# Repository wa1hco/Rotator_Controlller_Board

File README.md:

# Rotator_Controlller_Board
Board, Teensy, Relays for Ham M type rotators

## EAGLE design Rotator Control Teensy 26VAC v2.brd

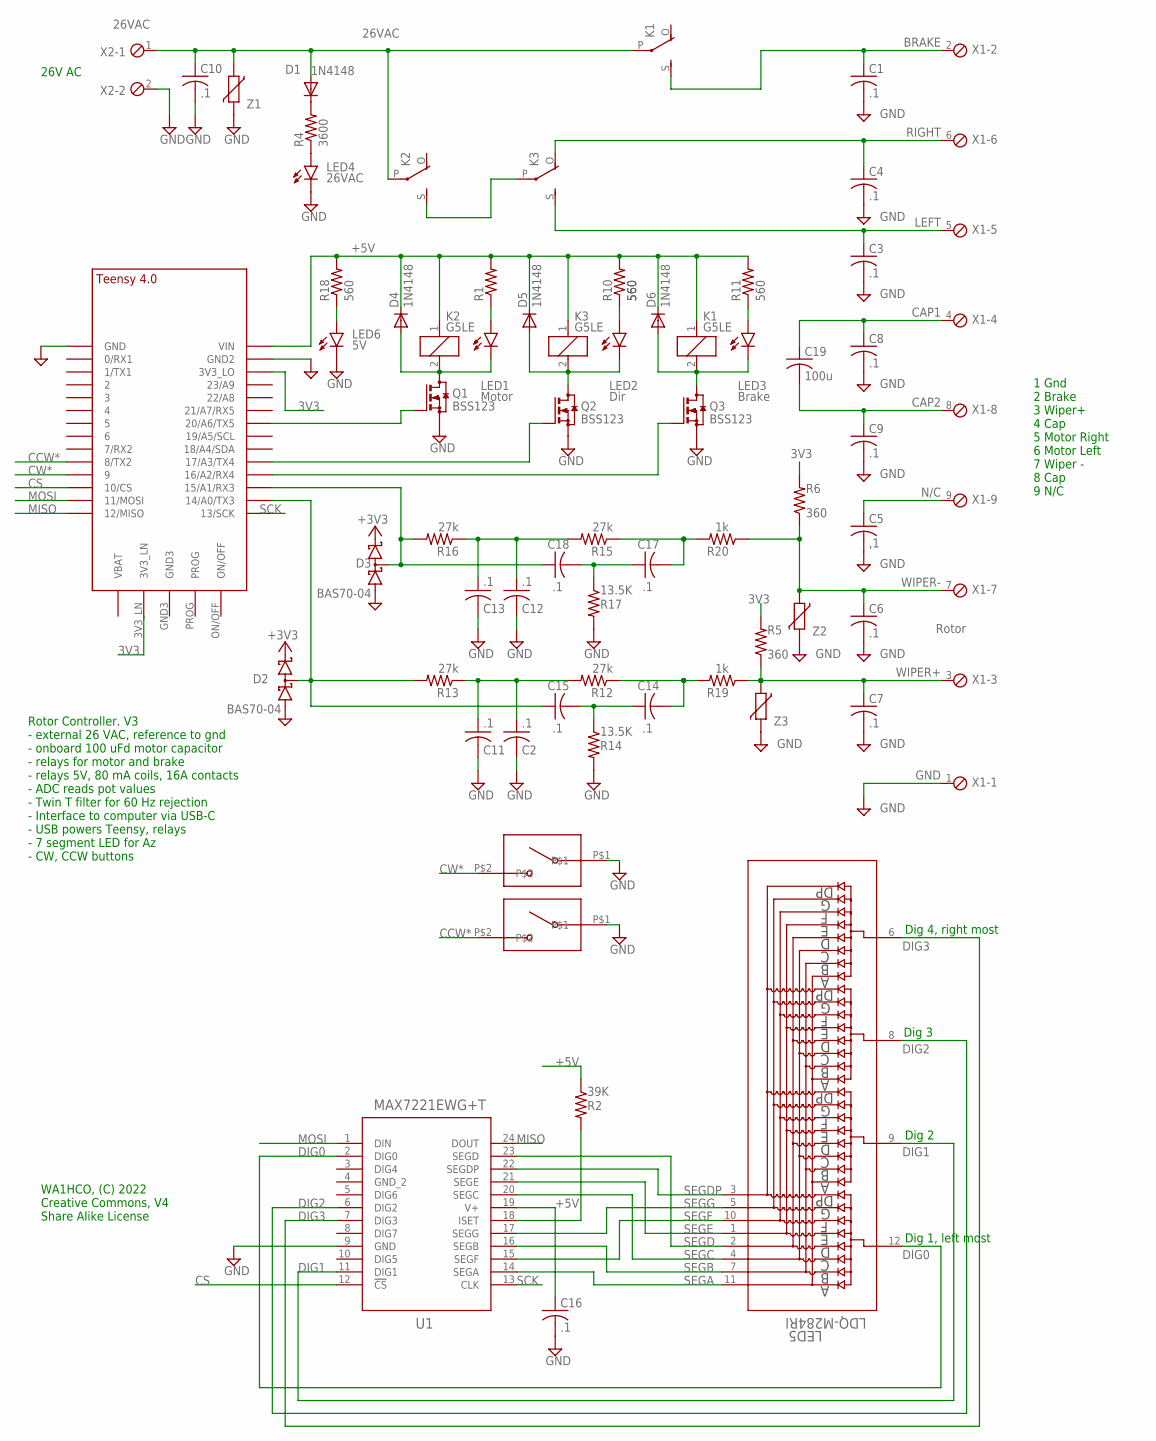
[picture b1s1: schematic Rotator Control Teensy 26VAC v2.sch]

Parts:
C1, C2, C3, C4, C6, C7, C8, C9, C10, C11, C12, C13, C14, C15, C16, C17, C18: .1; C1206
C5: ,1; C1206
C19: 100u; C4220
CCW: SWITCH_AEXIT_6X6X9.5; PUSHBUTTON_6X6
CW: SWITCH_AEXIT_6X6X9.5; PUSHBUTTON_6X6
D1, D4, D5, D6: 1N4148; SOD-123
D2, D3: BAS70-04; SOT23
K1, K2, K3: G5LE
LED1: Motor; LED3MM
LED2: Dir; LED3MM
LED3: Brake; LED3MM
LED4: 26VAC; LED3MM
LED5: LDQ-M284RI; LDQ-M284RI_LUM
LED6: 5V; LED3MM
Q1, Q2, Q3: BSS123; SOT23
R1, R10, R11, R18: 560; R0805
R2: 39K; R0603
R4: 3600; R0805
R5, R6: 360; R0805
R12, R13, R15, R16: 27k; R0805
R14, R17: 13.5K; R0805
R19, R20: 1k; R0805
U1: MAX7221EWG+T; 21-0042_W24+1_MXM
U$1: TEENSY_4.0
X1: Rotor; 9POL254
X2: 26VAC; 2POL254
Z1, Z2, Z3: VARISTORCN1206; CT/CN1206

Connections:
3V3: D2.2 (C2), D3.2 (C2), R5.2, R6.2, U$1.3V3_LN, U$1.3V3_LO
26VAC: C10.1, D1.A, K1.P, K2.P, X2.1, Z1.1
+5V: C16.1, D4.C, D5.C, D6.C, K1.1, K2.1, K3.1, R1.2, R2.1, R10.2, R11.2, R18.2, U1.19 (V+), U$1.VIN
BRAKE: C1.1, K1.S, X1.2
CAP1: C8.1, C19.P$1 (1), X1.4
CAP2: C9.1, C19.P$2 (2), X1.8
CCW*: CCW.P$2, U$1.8 (8/TX2)
CS: U1.12 (!CS), U$1.10/CS
CW*: CW.P$2, U$1.9/CS (9)
DIG0: LED5.12, U1.2 (DIG0)
DIG1: LED5.9, U1.11 (DIG1)
DIG2: LED5.8, U1.6 (DIG2)
DIG3: LED5.6, U1.7 (DIG3)
GND: C1.2, C2.2, C3.2, C4.2, C5.2, C6.2, C7.2, C8.2, C9.2, C10.2, C11.2, C12.2, C13.2, C16.2, CCW.P$1, CW.P$1, D2.1 (A1), D3.1 (A1), LED4.K (C), LED6.K (C), Q1.2 (S), Q2.2 (S), Q3.2 (S), R14.2, R17.2, U1.9 (GND), U$1.GND, U$1.GND2, X1.1, X2.2, Z1.2, Z2.2, Z3.2
ISET: R2.2, U1.18 (ISET)
LEFT: C4.1, K3.O, X1.6
MISO: U1.24 (DOUT), U$1.12/MISO
MOSI: U1.1 (DIN), U$1.11/MOSI
unnamed: C17.2, R15.1, R20.2
unnamed: LED6.A, R18.1
unnamed: C14.2, R12.1, R19.2
unnamed: LED1.A, R1.1
unnamed: LED2.A, R10.1
unnamed: LED3.A, R11.1
unnamed: C15.1, D2.3 (C1A2), R13.2, U$1.14/A0 (14/A0/TX3)
unnamed: K2.S, K3.P
unnamed: D4.A, K2.2, LED1.K (C), Q1.3 (D)
unnamed: D5.A, K3.2, LED2.K (C), Q2.3 (D)
unnamed: D6.A, K1.2, LED3.K (C), Q3.3 (D)
unnamed: Q3.1 (G), U$1.16/A2 (16/A2/RX4)
unnamed: Q1.1 (G), U$1.20/A6 (20/A6/TX5)
unnamed: Q2.1 (G), U$1.17/A3 (17/A3/TX4)
unnamed: C2.1, C11.1, R12.2, R13.1
unnamed: C14.1, C15.2, R14.1
unnamed: C12.1, C13.1, R15.2, R16.1
unnamed: C17.1, C18.2, R17.1
unnamed: C18.1, D3.3 (C1A2), R16.2, U$1.15/A1 (15/A1/RX3)
unnamed: D1.C, R4.2
unnamed: LED4.A, R4.1
N/C: C5.1, X1.9
RIGHT: C3.1, K3.S, X1.5
SCK: U1.13 (CLK), U$1.13/SCK
SEGA: LED5.11, U1.14 (SEGA)
SEGB: LED5.7, U1.16 (SEGB)
SEGC: LED5.4, U1.20 (SEGC)
SEGD: LED5.2, U1.23 (SEGD)
SEGDP: LED5.3, U1.22 (SEGDP)
SEGE: LED5.1, U1.21 (SEGE)
SEGF: LED5.10, U1.15 (SEGF)
SEGG: LED5.5, U1.17 (SEGG)
WIPER+: C7.1, R5.1, R19.1, X1.3, Z3.1
WIPER-: C6.1, R6.1, R20.1, X1.7, Z2.1

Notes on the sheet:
Rotor Controller. V3 - external 26 VAC, reference to gnd - onboard 100 uFd motor capacitor - relays for motor and brake - relays 5V, 80 mA coils, 16A contacts - ADC reads pot values - Twin T filter for 60 Hz rejection - Interface to computer via USB-C - USB powers Teensy, relays - 7 segment LED for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
1 Gnd 2 Brake 3 Wiper+ 4 Cap 5 Motor Right 6 Motor Left 7 Wiper - 8 Cap 9 N/C
26V AC
WA1HCO, (C) 2022 Creative Commons, V4 Share Alike License
Dig 4, right most
Dig 3
Dig 2
Dig 1, left most

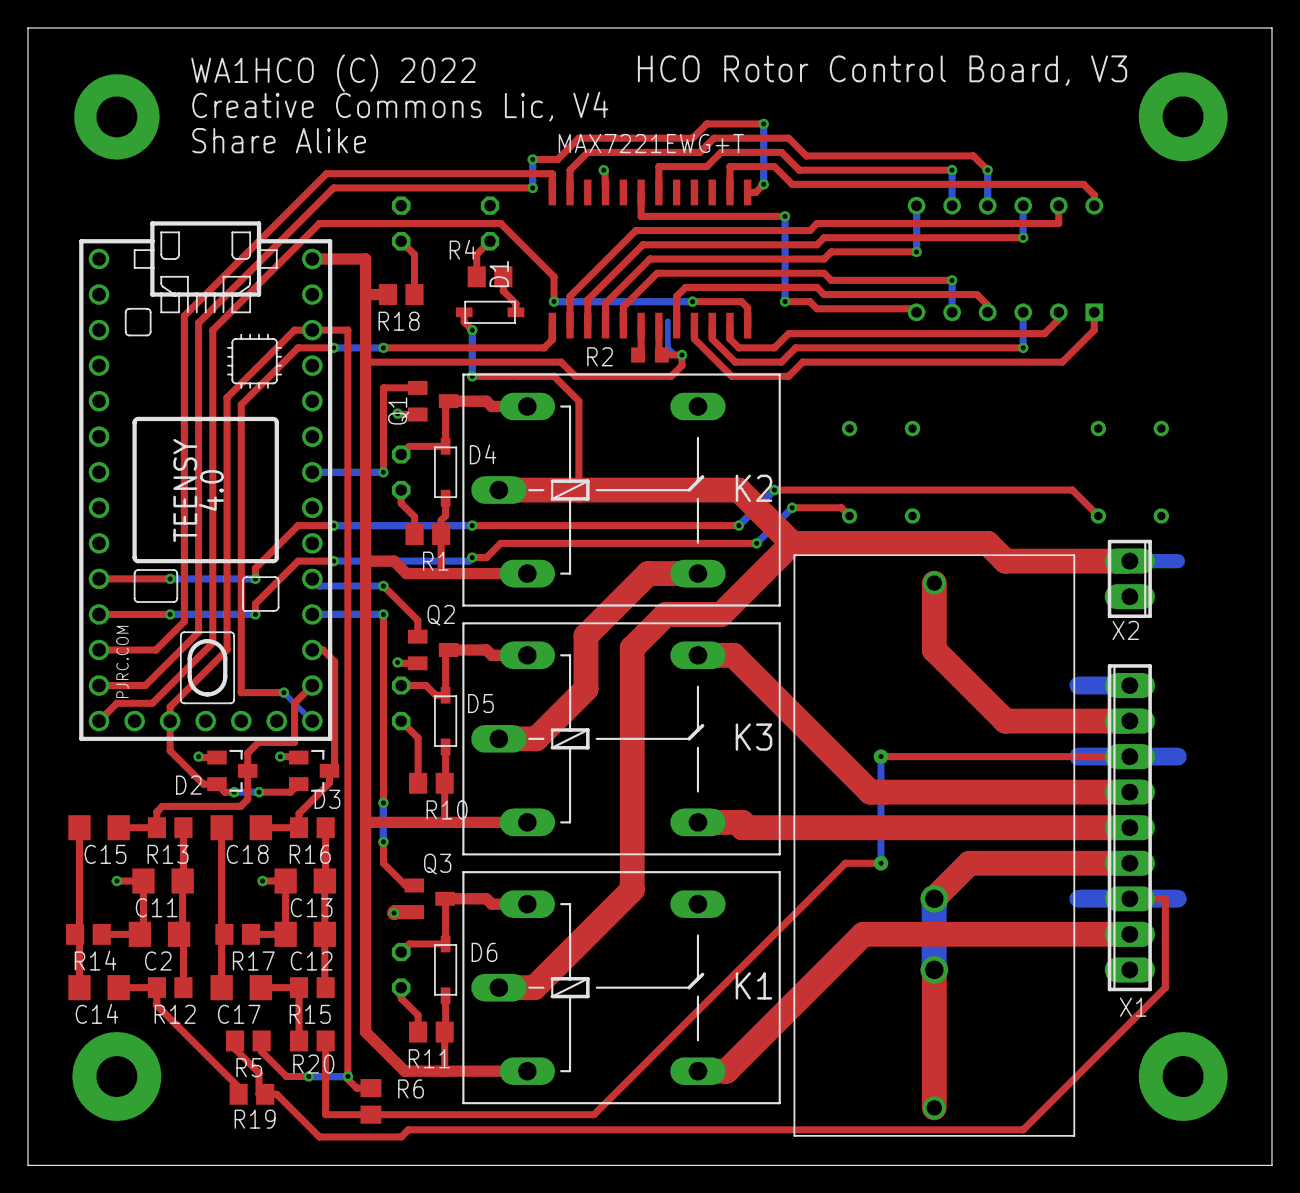
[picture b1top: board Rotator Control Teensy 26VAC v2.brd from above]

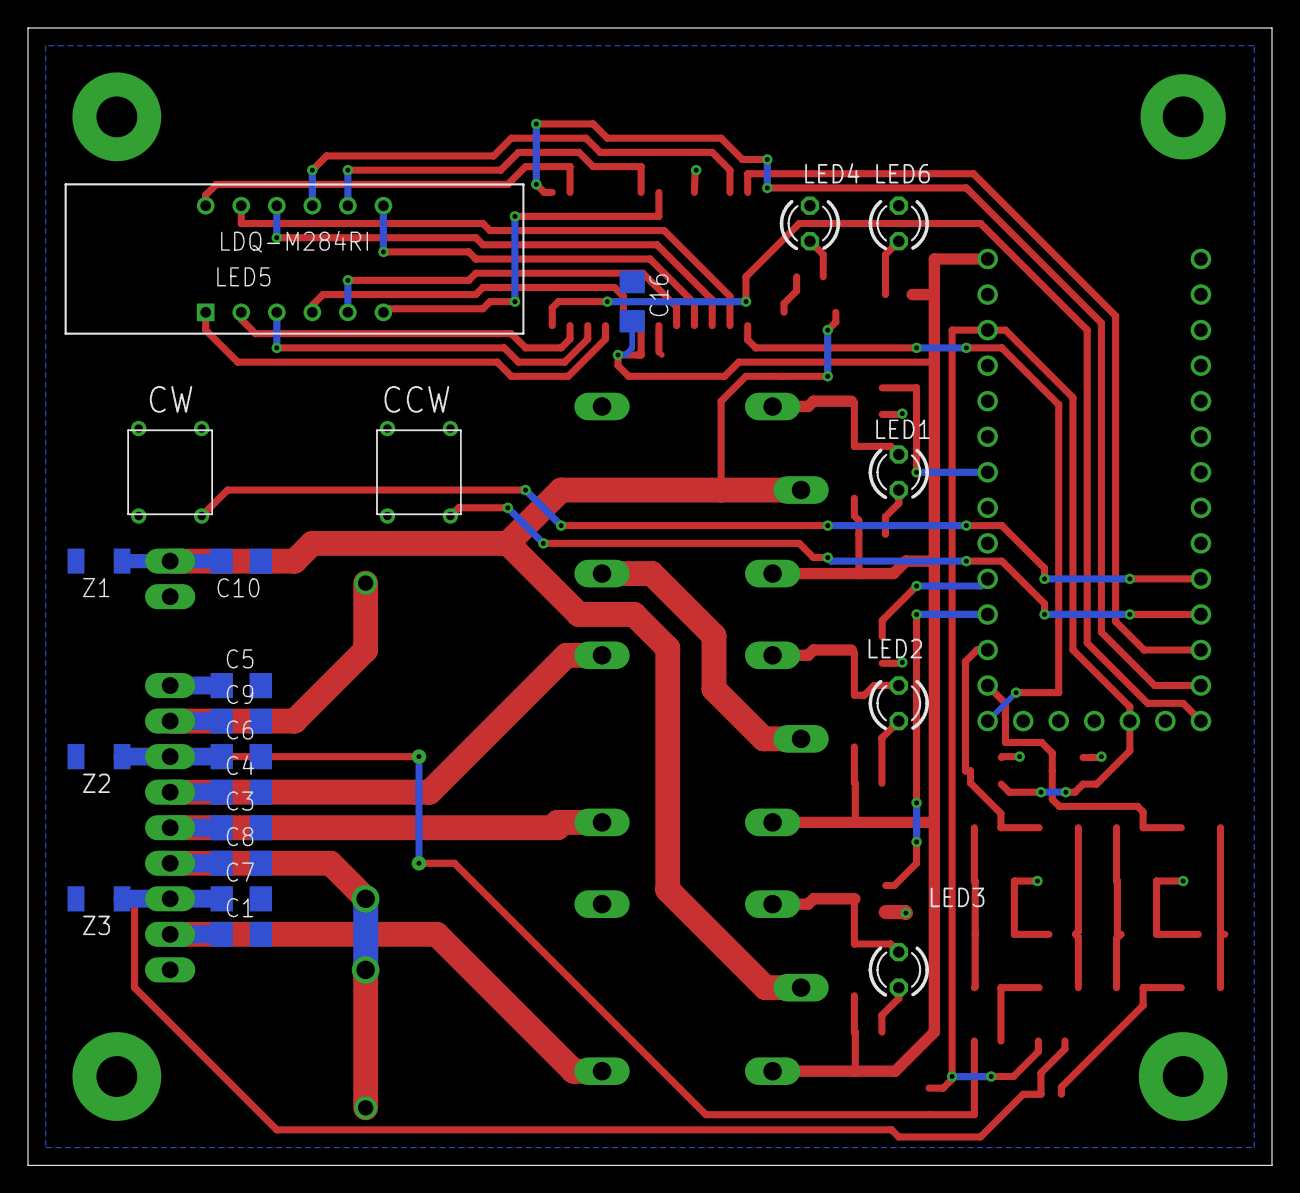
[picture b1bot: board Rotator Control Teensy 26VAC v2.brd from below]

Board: 2 copper layers, 88.9 x 81.3 mm, 62 parts (21 on the bottom side), 52 nets.

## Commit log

2022-03-11 Initial commit of Rotator Controller Board Teensy 4.0 processor, powered from USB C External 36 V AC transformer Relays for rotator interfacer 12V relays derived from 26V AC
2022-03-12 add 5V LED, polishing
2022-03-12 Simplified by running relays from 5V from USB 26V AC is only for the rotator
2022-03-14 switched LED to -.28 inch 4 digit plus driver with keyswitch capability
2022-03-14 Replaced license file with Creative Commons - Share Alike
2022-03-15 Released this version to OshPark for fab
2022-03-15 Add 5V power supply resistors to the rotor pot leads
2022-04-01 Add pullups on I2C lines Add holes for 7 segment LED with 0.4 in lead spacing
2022-04-03 move rotator pot pullups from 5V to regulated 3.3V. 5V varied from USB to USB and changed when relays activated...which changed the azimuth calibration
2022-04-12 Convert to MAX7221 LED driver Connect MAX7221 to SPI port Convert buttons to direct read with internal pullups
2022-04-12 Version 2 sent to OSHPark Add pullup on ISET Tweaked a bunch of layout, unecessarily
2022-05-07 Moved overvoltage protect diodes to after the 60 Hz notch filter. So the 60 Hz doesn't cause clipping and a DC shift when DC is near zero.
    Tweaked the layout accordingly.
2022-05-18 Move OVP diodes close to ADC

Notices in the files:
Rotator Control Teensy 26VAC v2.brd:
Creative Commons Lic, V4
parts and their libraries:
COPYRIGHT: Copyright (C) 2022 Ultra Librarian. All rights reserved.
